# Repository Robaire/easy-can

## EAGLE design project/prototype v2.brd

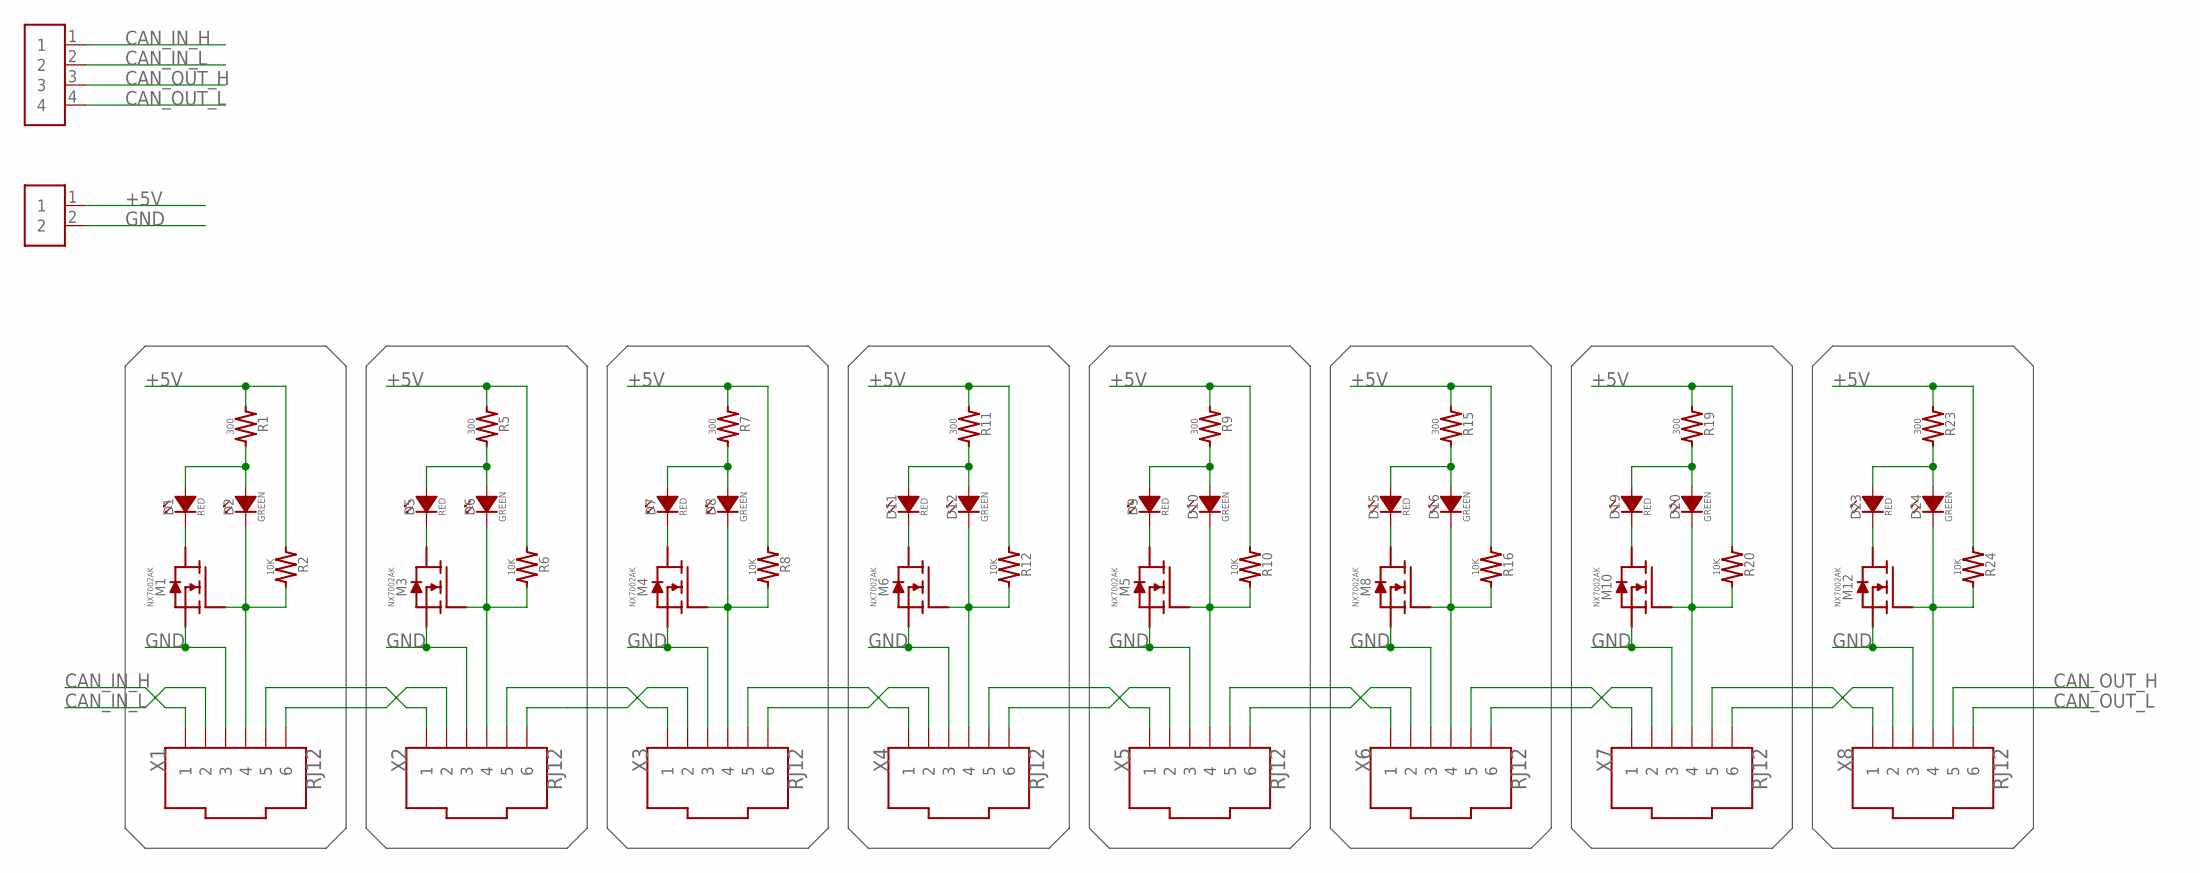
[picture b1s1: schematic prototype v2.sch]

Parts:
D1, D5, D7, D9, D11, D15, D19, D23: RED; 0603-LED
D2, D6, D8, D10, D12, D16, D20, D24: GREEN; 0603-LED
M1, M3, M4, M5, M6, M8, M10, M12: NX7002AK; SOT-23
R1, R5, R7, R9, R11, R15, R19, R23: 300; 0603
R2, R6, R8, R10, R12, R16, R20, R24: 10K; 0603
U$1: TERMINAL_BLOCK; TERMINALBLOCK-4
U$2: POWER_BLOCK; TERMINALBLOCK-2
X1, X2, X3, X4, X5, X6, X7, X8: RJ12

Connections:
+5V: R1.1, R2.1, R5.1, R6.1, R7.1, R8.1, R9.1, R10.1, R11.1, R12.1, R15.1, R16.1, R19.1, R20.1, R23.1, R24.1, U$2.1
CAN_IN_H: U$1.1, X1.1
CAN_IN_L: U$1.2, X1.2
CAN_OUT_H: U$1.3, X8.5
CAN_OUT_L: U$1.4, X8.6
GND: M1.2 (SOURCE), M3.2 (SOURCE), M4.2 (SOURCE), M5.2 (SOURCE), M6.2 (SOURCE), M8.2 (SOURCE), M10.2 (SOURCE), M12.2 (SOURCE), U$2.2, X1.3, X2.3, X3.3, X4.3, X5.3, X6.3, X7.3, X8.3
unnamed: D1.1 (-), M1.3 (DRAIN)
unnamed: D2.1 (-), M1.1 (GATE), R2.2, X1.4
unnamed: D1.2 (+), D2.2 (+), R1.2
unnamed: X1.5, X2.1
unnamed: X1.6, X2.2
unnamed: D5.1 (-), M3.3 (DRAIN)
unnamed: D6.1 (-), M3.1 (GATE), R6.2, X2.4
unnamed: D5.2 (+), D6.2 (+), R5.2
unnamed: X2.5, X3.1
unnamed: X2.6, X3.2
unnamed: D9.1 (-), M5.3 (DRAIN)
unnamed: D10.1 (-), M5.1 (GATE), R10.2, X5.4
unnamed: D7.1 (-), M4.3 (DRAIN)
unnamed: D8.1 (-), M4.1 (GATE), R8.2, X3.4
unnamed: D7.2 (+), D8.2 (+), R7.2
unnamed: X3.5, X4.1
unnamed: X3.6, X4.2
unnamed: D9.2 (+), D10.2 (+), R9.2
unnamed: X5.5, X6.1
unnamed: X5.6, X6.2
unnamed: X4.6, X5.2
unnamed: D11.1 (-), M6.3 (DRAIN)
unnamed: D12.1 (-), M6.1 (GATE), R12.2, X4.4
unnamed: D11.2 (+), D12.2 (+), R11.2
unnamed: X4.5, X5.1
unnamed: D15.1 (-), M8.3 (DRAIN)
unnamed: D16.1 (-), M8.1 (GATE), R16.2, X6.4
unnamed: D15.2 (+), D16.2 (+), R15.2
unnamed: X6.5, X7.1
unnamed: X6.6, X7.2
unnamed: D19.1 (-), M10.3 (DRAIN)
unnamed: D20.1 (-), M10.1 (GATE), R20.2, X7.4
unnamed: D19.2 (+), D20.2 (+), R19.2
unnamed: X7.5, X8.1
unnamed: X7.6, X8.2
unnamed: D23.1 (-), M12.3 (DRAIN)
unnamed: D24.1 (-), M12.1 (GATE), R24.2, X8.4
unnamed: D23.2 (+), D24.2 (+), R23.2

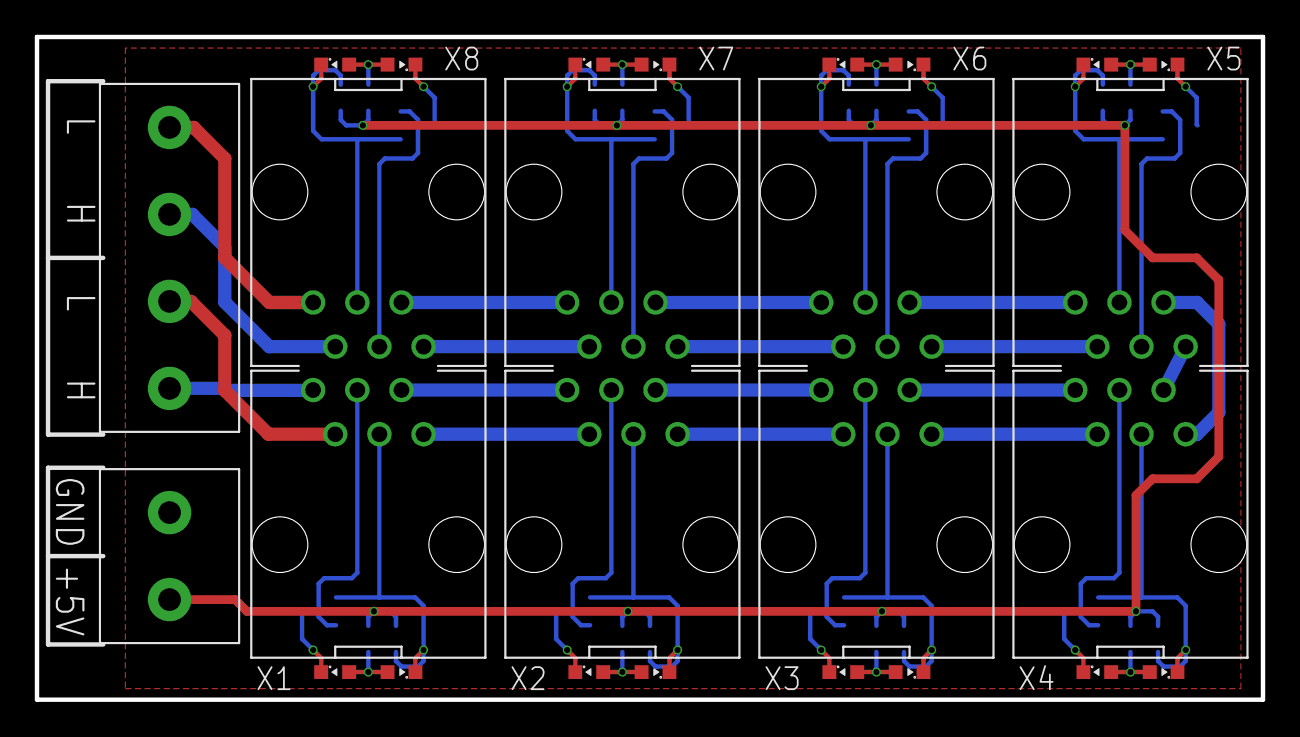
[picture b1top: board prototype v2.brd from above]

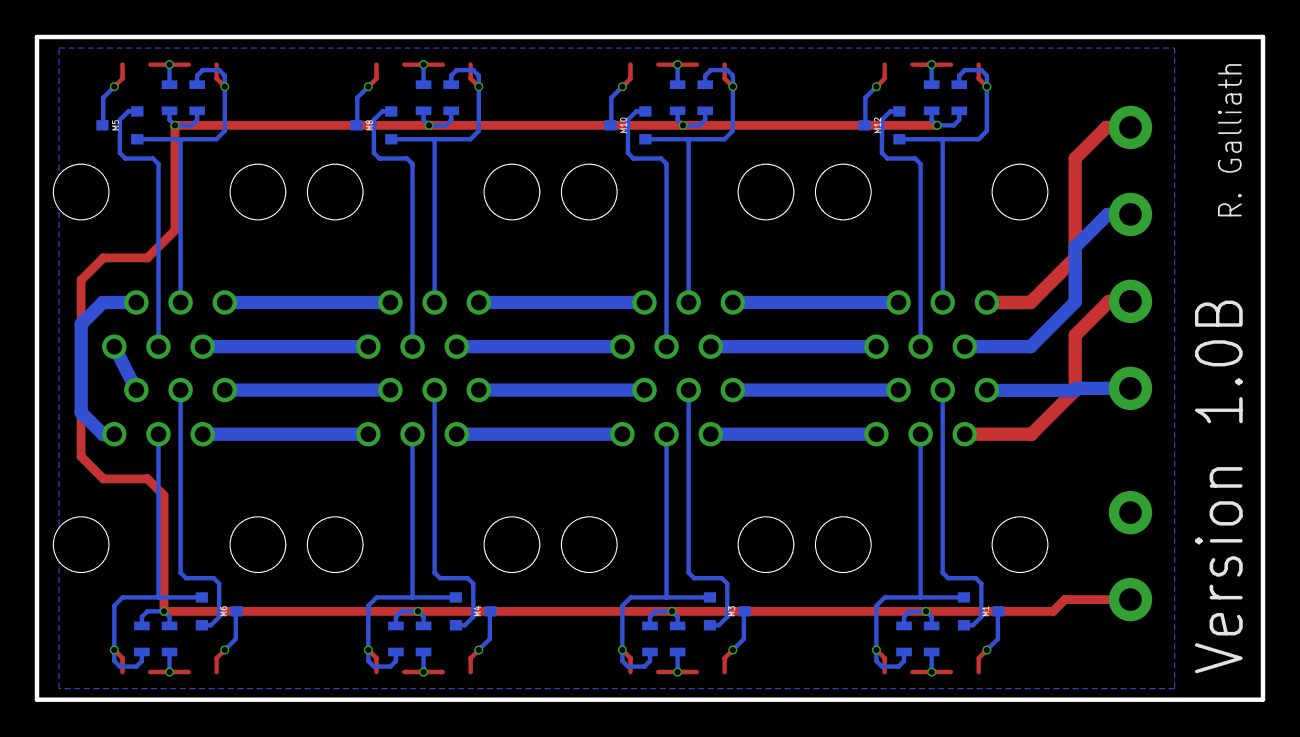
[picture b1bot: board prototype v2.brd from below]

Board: 2 copper layers, 70.5 x 38.1 mm, 50 parts (24 on the bottom side), 44 nets.

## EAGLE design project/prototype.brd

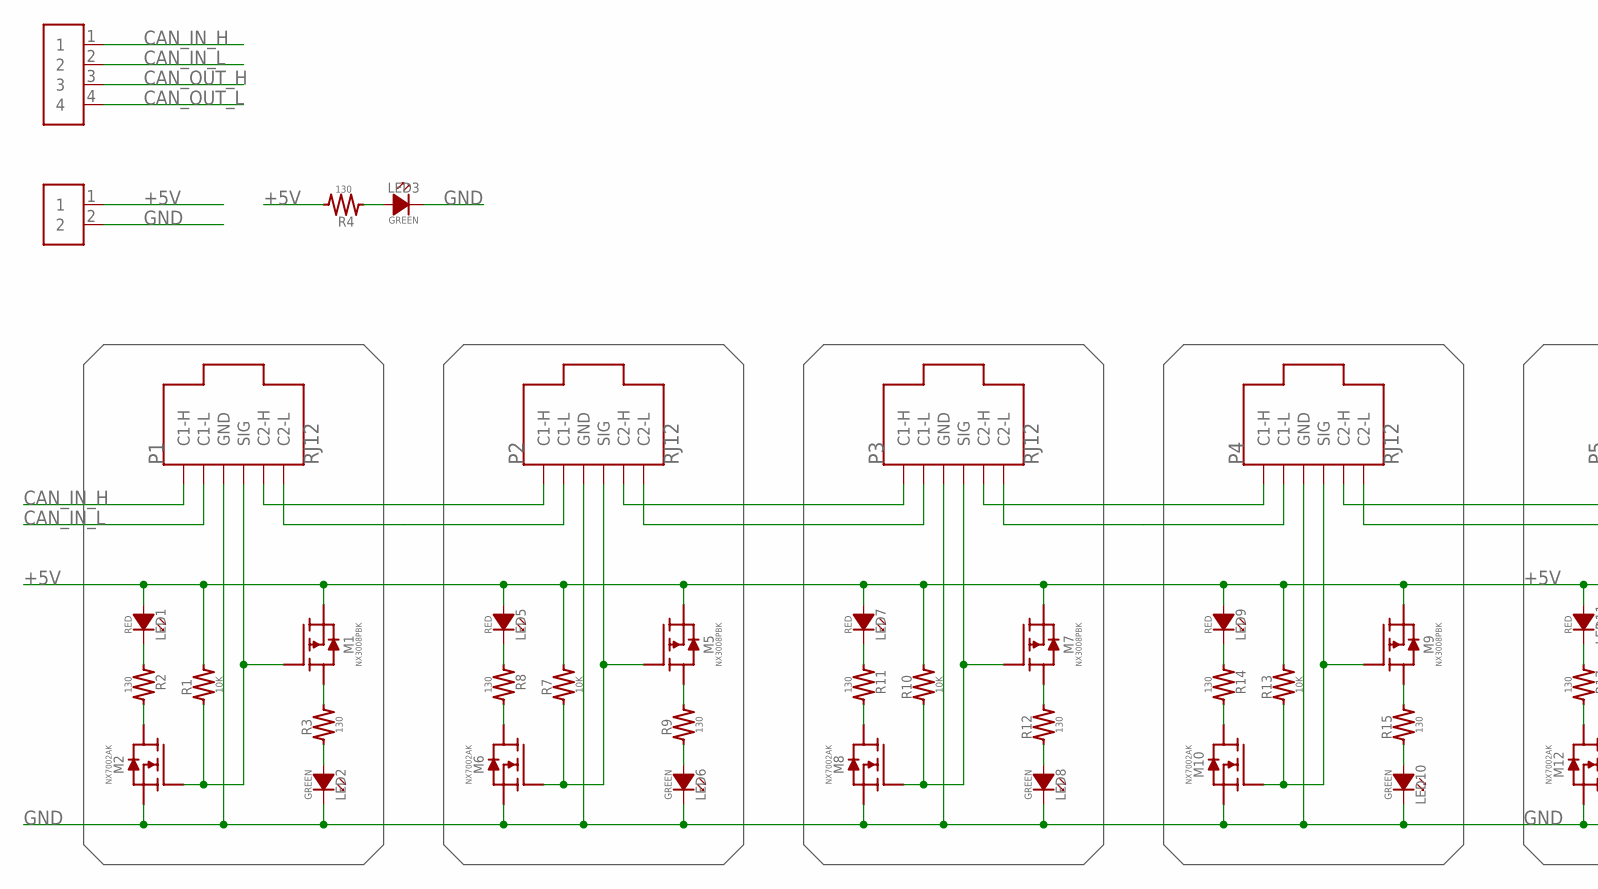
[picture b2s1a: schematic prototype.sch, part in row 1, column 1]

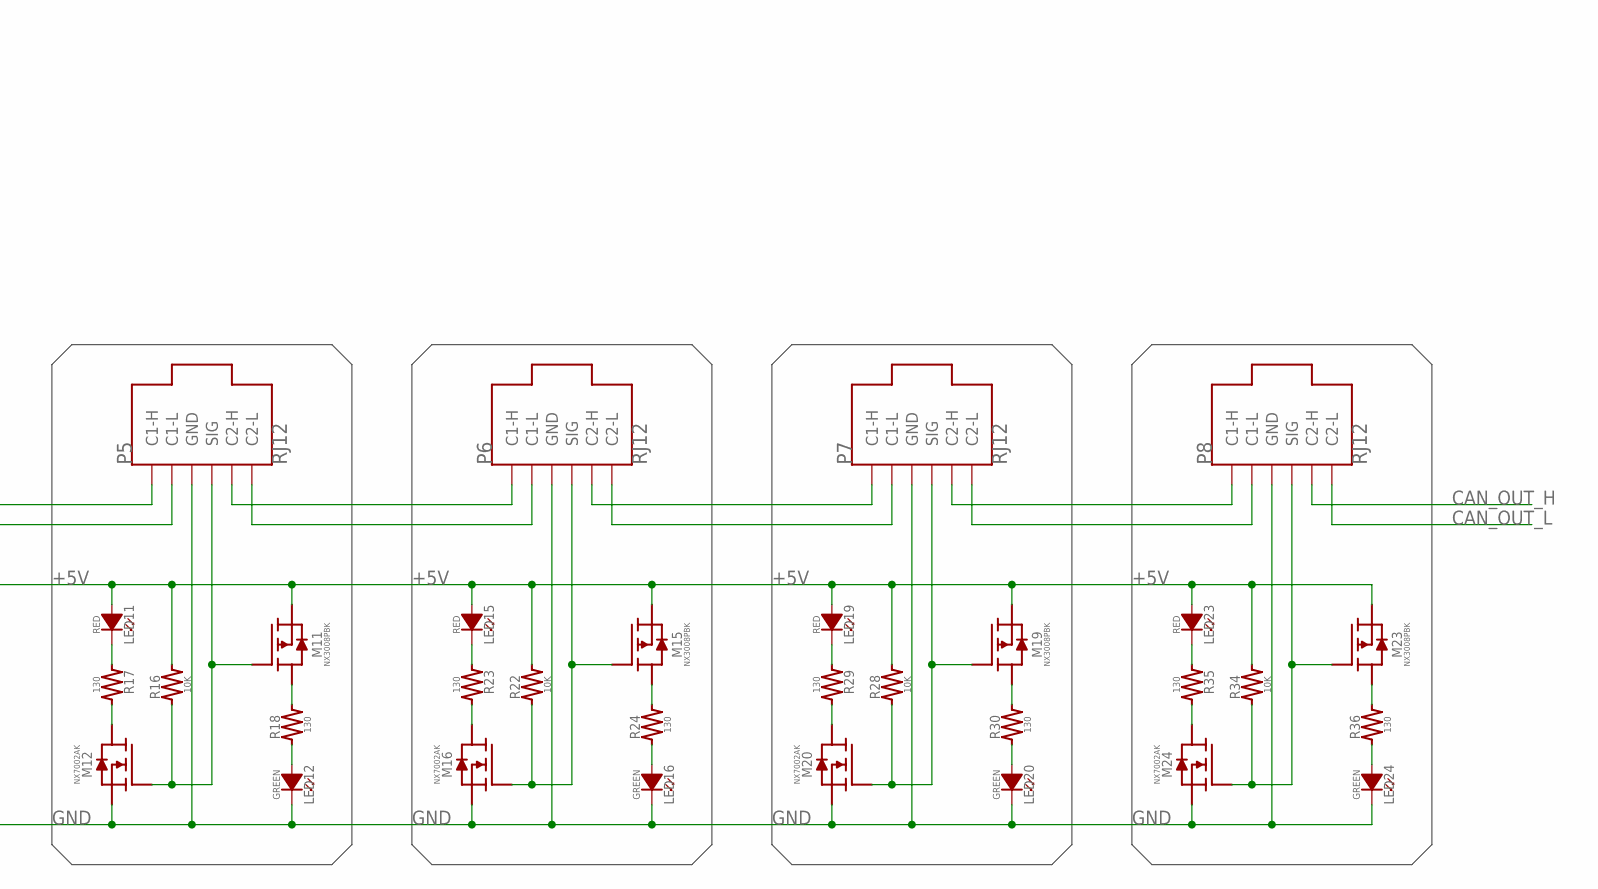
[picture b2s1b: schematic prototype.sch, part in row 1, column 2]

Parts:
LED1, LED5, LED7, LED9, LED11, LED15, LED19, LED23: RED; 0603-LED
LED2, LED3, LED6, LED8, LED10, LED12, LED16, LED20, LED24: GREEN; 0603-LED
M1, M5, M7, M9, M11, M15, M19, M23: NX3008PBK; SOT23
M2, M6, M8, M10, M12, M16, M20, M24: NX7002AK; SOT23
P1, P2, P3, P4, P5, P6, P7, P8: RJ12
R1, R7, R10, R13, R16, R22, R28, R34: 10K; 0402
R2, R3, R4, R8, R9, R11, R12, R14, R15, R17, R18, R23, R24, R29, R30, R35, R36: 130; 0402
U$1: TERMINAL_BLOCK; TERMINALBLOCK-4
U$2: POWER_BLOCK; TERMINALBLOCK-2

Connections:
+5V: LED1.2 (+), LED5.2 (+), LED7.2 (+), LED9.2 (+), LED11.2 (+), LED15.2 (+), LED19.2 (+), LED23.2 (+), M1.2 (SOURCE), M5.2 (SOURCE), M7.2 (SOURCE), M9.2 (SOURCE), M11.2 (SOURCE), M15.2 (SOURCE), M19.2 (SOURCE), M23.2 (SOURCE), R1.2, R4.2, R7.2, R10.2, R13.2, R16.2, R22.2, R28.2, R34.2, U$2.1
CAN_IN_H: P1.1 (C1-H), U$1.1
CAN_IN_L: P1.2 (C1-L), U$1.2
CAN_OUT_H: P8.5 (C2-H), U$1.3
CAN_OUT_L: P8.6 (C2-L), U$1.4
GATE1: M1.1 (GATE), M2.1 (GATE), P1.4 (SIG), R1.1
GATE2: M5.1 (GATE), M6.1 (GATE), P2.4 (SIG), R7.1
GATE3: M7.1 (GATE), M8.1 (GATE), P3.4 (SIG), R10.1
GATE4: M9.1 (GATE), M10.1 (GATE), P4.4 (SIG), R13.1
GATE5: M11.1 (GATE), M12.1 (GATE), P5.4 (SIG), R16.1
GATE7: M15.1 (GATE), M16.1 (GATE), P6.4 (SIG), R22.1
GATE9: M19.1 (GATE), M20.1 (GATE), P7.4 (SIG), R28.1
GATE11: M23.1 (GATE), M24.1 (GATE), P8.4 (SIG), R34.1
GND: LED2.1 (-), LED3.1 (-), LED6.1 (-), LED8.1 (-), LED10.1 (-), LED12.1 (-), LED16.1 (-), LED20.1 (-), LED24.1 (-), M2.2 (SOURCE), M6.2 (SOURCE), M8.2 (SOURCE), M10.2 (SOURCE), M12.2 (SOURCE), M16.2 (SOURCE), M20.2 (SOURCE), M24.2 (SOURCE), P1.3 (GND), P2.3 (GND), P3.3 (GND), P4.3 (GND), P5.3 (GND), P6.3 (GND), P7.3 (GND), P8.3 (GND), U$2.2
unnamed: LED3.2 (+), R4.1
unnamed: M1.3 (DRAIN), R3.2
unnamed: LED2.2 (+), R3.1
unnamed: LED1.1 (-), R2.1
unnamed: M2.3 (DRAIN), R2.2
unnamed: P1.5 (C2-H), P2.1 (C1-H)
unnamed: M7.3 (DRAIN), R12.2
unnamed: M5.3 (DRAIN), R9.2
unnamed: LED6.2 (+), R9.1
unnamed: LED5.1 (-), R8.1
unnamed: M6.3 (DRAIN), R8.2
unnamed: LED8.2 (+), R12.1
unnamed: P1.6 (C2-L), P2.2 (C1-L)
unnamed: P2.5 (C2-H), P3.1 (C1-H)
unnamed: P2.6 (C2-L), P3.2 (C1-L)
unnamed: LED7.1 (-), R11.1
unnamed: M8.3 (DRAIN), R11.2
unnamed: M11.3 (DRAIN), R18.2
unnamed: LED12.2 (+), R18.1
unnamed: P3.5 (C2-H), P4.1 (C1-H)
unnamed: P3.6 (C2-L), P4.2 (C1-L)
unnamed: M9.3 (DRAIN), R15.2
unnamed: LED10.2 (+), R15.1
unnamed: LED9.1 (-), R14.1
unnamed: M10.3 (DRAIN), R14.2
unnamed: LED11.1 (-), R17.1
unnamed: M12.3 (DRAIN), R17.2
unnamed: P4.5 (C2-H), P5.1 (C1-H)
unnamed: P4.6 (C2-L), P5.2 (C1-L)
unnamed: M15.3 (DRAIN), R24.2
unnamed: LED16.2 (+), R24.1
unnamed: LED15.1 (-), R23.1
unnamed: M16.3 (DRAIN), R23.2
unnamed: P5.5 (C2-H), P6.1 (C1-H)
unnamed: P5.6 (C2-L), P6.2 (C1-L)
unnamed: M19.3 (DRAIN), R30.2
unnamed: LED20.2 (+), R30.1
unnamed: LED19.1 (-), R29.1
unnamed: M20.3 (DRAIN), R29.2
unnamed: P6.5 (C2-H), P7.1 (C1-H)
unnamed: P6.6 (C2-L), P7.2 (C1-L)
unnamed: M23.3 (DRAIN), R36.2
unnamed: LED24.2 (+), R36.1
unnamed: LED23.1 (-), R35.1
unnamed: M24.3 (DRAIN), R35.2
unnamed: P7.5 (C2-H), P8.1 (C1-H)
unnamed: P7.6 (C2-L), P8.2 (C1-L)

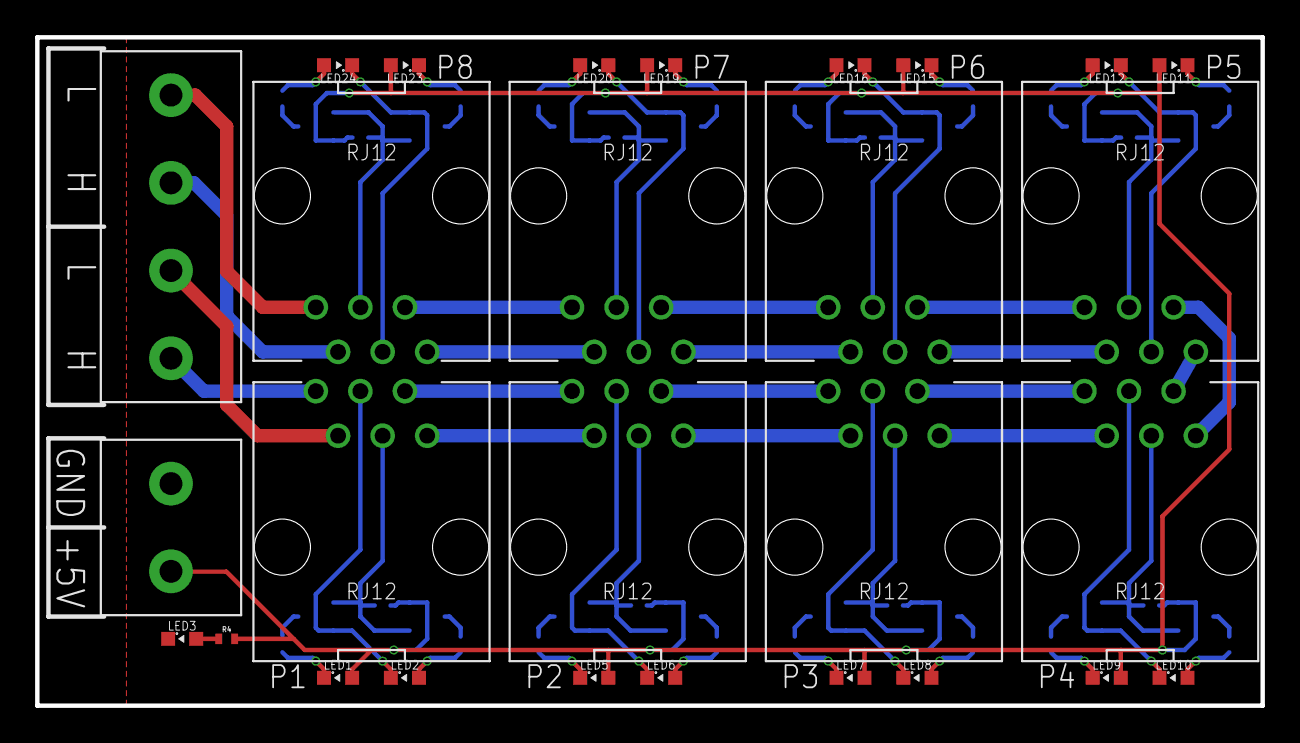
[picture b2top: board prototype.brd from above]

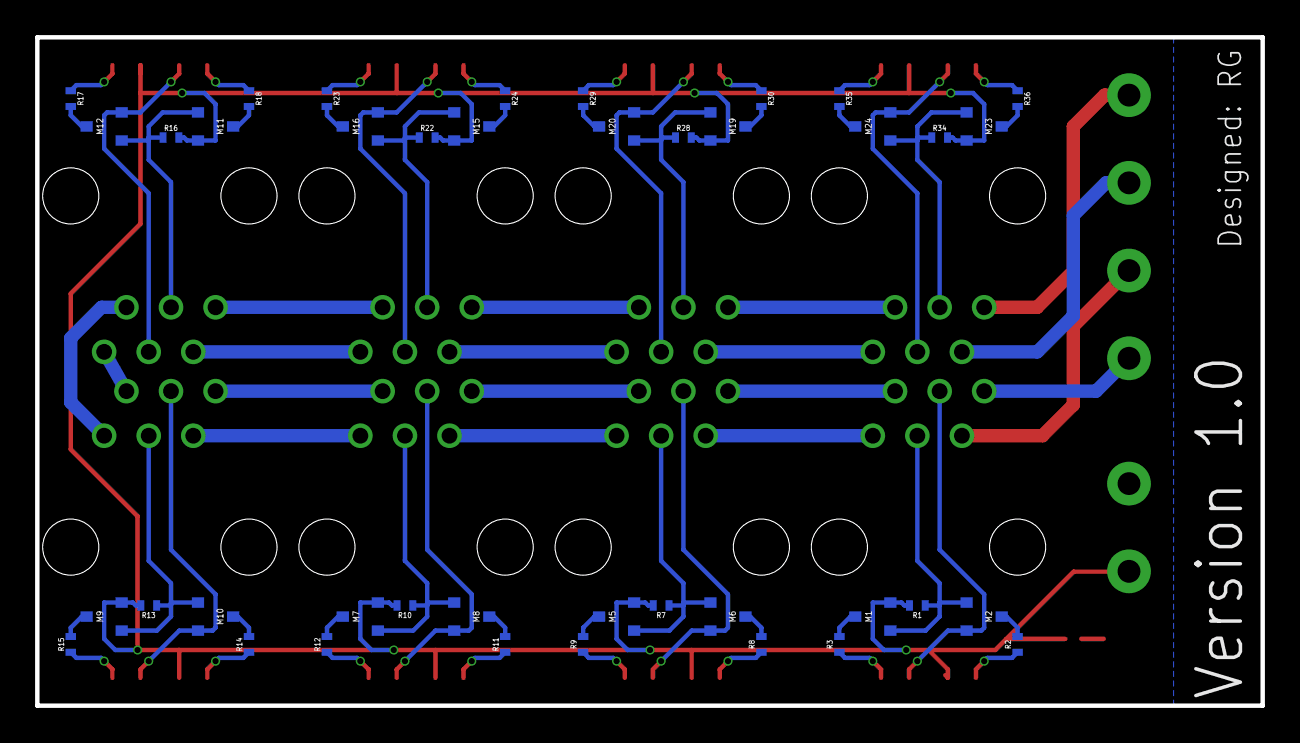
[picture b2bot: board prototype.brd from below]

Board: 2 copper layers, 69.8 x 38.1 mm, 68 parts (40 on the bottom side), 61 nets.

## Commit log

2019-07-17 Add datasheets
2019-07-17 Create component library
2019-07-17 Create eagle project
2019-07-17 Create prototype board
2019-07-17 Ignore eagle backup files
2019-07-17 Add library
2019-07-17 Add photo mosfet, mosfet, and RJ12 components
2019-07-17 Add components
2019-07-18 Add LED package and symbol
2019-07-18 Add red LED
2019-07-26 Add P-Channel Mosfet Documentation
2019-07-26 Create P-Channel Mosfet and Green LED
2019-07-26 Correct RJ12 name and value layers
2019-07-26 Add indicator schematic
2019-07-26 Add indicator LED layout
2019-07-27 Create breakout board
2019-07-27 Add input terminal blocks
2019-07-27 Add terminal blocks
2019-07-27 Increase trace size
2019-07-27 Change power LED layout
2019-07-28 Combine components
2019-07-28 Create V2 prototype board
2019-07-31 Correct RJ12 layout
2019-07-31 Update RJ12 position
